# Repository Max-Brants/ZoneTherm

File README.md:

<picture>
  <source media="(prefers-color-scheme: dark)" srcset="brand/zonetherm-logo-dark.svg">
  
</picture>

# ZoneTherm

**A 7-zone OpenTherm heating/cooling controller.** ESP32-S3 firmware, KiCad
hardware, and a Svelte web UI for a house where every room has its own
OpenTherm room thermostat but the plant has a single manifold of zone valves.

Version 1.0.0.

---

## The idea

A normal OpenTherm setup is one thermostat talking to one boiler. ZoneTherm sits
in the middle of seven of those conversations at once:

```
 Room thermostat 1  ──OpenTherm──┐
 Room thermostat 2  ──OpenTherm──┤
        ...                      ├──►  ZoneTherm  ──I²C──►  MCP23017  ──►  7 zone valves
 Room thermostat 7  ──OpenTherm──┘        │
                                          ├──► Ethernet / WiFi ──► MQTT ──► Home Assistant
                                          └──► Web UI + REST API
```

To each thermostat, ZoneTherm **pretends to be a boiler**. It answers every
OpenTherm request the thermostat makes, so the thermostat behaves exactly as it
would on a real appliance — it shows a flame, it runs its own schedule, it lets
you turn the dial. While answering, ZoneTherm captures the two numbers that
matter: the room temperature the thermostat measured, and the setpoint it is
asking for.

It then makes the only decision that is actually its own: for each thermostat,
should heat be flowing? That is a bang-bang comparison with a symmetric
hysteresis band, and it lives in exactly one function
([`ClimateLogic::valveWanted`](Code/src/domain/ClimateLogic.h)).

Each thermostat drives a **valve set** — one valve, or several. A room with
three underfloor loops has three actuators and one thermostat, and they open
and close together in a single I²C write.
[`ValvePlan::solve`](Code/src/domain/ValvePlan.h) turns the seven per-room
answers into the one byte the expander wants. A valve belongs to at most one
thermostat, which the web UI enforces by greying out valves already taken and
the API enforces by rejecting the save.

One **season** — heating or cooling — applies to the whole plant, because
there is one set of pipes. Individual zones can be disabled, but they cannot
disagree about which direction the water is going.

Setpoints can also be pushed the other way. A setpoint sent from Home Assistant
or the web UI is written back to the room thermostat over OpenTherm's
`TrOverride` mechanism, so the wall unit shows the new target too.

### Things worth knowing before you build one

- ZoneTherm **is not a gateway.** There is no upstream boiler connection in the
  main firmware. It terminates all seven OpenTherm links itself and drives
  valves; your boiler is expected to be commanded by something else (a valve
  end-switch loop, or its own thermostat input).
- A zone whose thermostat has never reported a room temperature keeps its valves
  **closed**, as does a disabled zone. There is no fail-open.
- The same goes for the two ways a valve set can be misconfigured: a thermostat
  with **no valves** keeps tracking its band and reporting demand but opens
  nothing, and a valve **claimed by nobody** never opens. Both are flagged on
  the config page and logged at boot rather than silently guessed at.
- Upgrading from a pre-valve-set firmware leaves the wiring alone: every
  thermostat comes up owning the one valve on its own channel, exactly as
  before.
- `boilerTemp`, `flameOn`, `fault` and friends exist in the zone state and are
  parsed off the wire, but only `modulation` is currently exported as a Home
  Assistant sensor.

---

## Repository layout

| Path | What it is |
|---|---|
| [Code/](Code/) | ESP32-S3 firmware (ESP-IDF via PlatformIO). See [Code/README.md](Code/README.md) for the architecture write-up. |
| [Code/webui/](Code/webui/) | Svelte 5 + Vite + TypeScript single-page app, built into `Code/data/` and flashed as a LittleFS image. |
| [pcb/](pcb/) | KiCad 8 project `ZoneTherm.kicad_pro` — seven OpenTherm slave interfaces, W5500 Ethernet, MCP23017 valve bank. Fabrication outputs in `GERBER/`, `production/`, `jlcpcb/`. |
| [enclosure/](enclosure/) | Three-part printed case, generated from the KiCad board by a script rather than measured off it. See [enclosure/README.md](enclosure/README.md) — **read the mains section before printing one**. |
| [.github/workflows/](.github/workflows/) | Release workflow that builds and publishes the OTA assets. |

---

## Hardware

**Board:** ESP32-S3-DevKitC-1 (16 MB flash, no PSRAM required).

**Pinout** — from [`Code/src/app/Pins.h`](Code/src/app/Pins.h), matching the
`Thermos_In_X` / `Thermos_Out_X` nets on the schematic:

| Zone | In (GPIO) | Out (GPIO) |
|---|---|---|
| 1 | 2 | 1 |
| 2 | 42 | 41 |
| 3 | 40 | 39 |
| 4 | 48 | 47 |
| 5 | 20 | 19 |
| 6 | 18 | 17 |
| 7 | 16 | 15 |

I²C to the MCP23017 valve expander: `SDA = 4`, `SCL = 5`.
Ethernet is a W5500 on SPI — see U3 on `ZoneTherm.kicad_pcb`.

**Flash layout** ([`Code/partitions.csv`](Code/partitions.csv)) — dual OTA app
slots plus a large filesystem, which is what makes both firmware *and* web UI
updatable over the air:

| Partition | Offset | Size |
|---|---|---|
| `nvs` | 0x9000 | 16 KB |
| `otadata` | 0xd000 | 8 KB |
| `ota_0` | 0x10000 | 3 MB |
| `ota_1` | 0x310000 | 3 MB |
| `littlefs` | 0x610000 | ~10 MB |

---

## Getting started

### 1. Build and flash

PlatformIO is the primary path. On Windows, `pio` may not be on `PATH` —
`~/.platformio/penv/Scripts/platformio.exe` is the full path.

```bash
cd Code
pio run                 # build firmware
pio run -t upload       # flash over USB
pio run -t buildfs      # build the web UI into data/ and pack a LittleFS image
pio run -t uploadfs     # flash the filesystem
pio run -t monitor      # serial console @ 115200
```

`buildfs`/`uploadfs` run [`webui_build.py`](Code/webui_build.py) first, so the
image always contains the current `webui/src` rather than a stale `data/`.

Raw ESP-IDF (`idf.py build`) also works.

**Flash both** the firmware and the filesystem on a new board. Firmware alone
boots but serves no web UI.

### 2. First boot

Network bring-up is automatic and layered:

1. **Ethernet** (DHCP, zero configuration) is tried first and always wins — if
   the link comes up at any later point, WiFi is shut down and Ethernet takes
   over.
2. No Ethernet link → joins the configured **WiFi** as a station.
3. No WiFi configured, or it never gets an IP within 60 s → opens an open
   provisioning access point **`ZoneTherm-<ID>`** at <http://192.168.4.1/>.

`<ID>` is the last three bytes of the MAC in hex, so each controller is
distinct on a shared network.

The device also advertises itself over mDNS as `zonetherm-<ID>.local`.

### 3. Configure

Everything is runtime-configurable — **no credentials live in the source
tree**. Open `http://<device>/config` (or `POST /api/config`) and set:

- hostname
- WiFi SSID / password
- MQTT broker host, port, username, password, base topic, discovery prefix
- season (heating / cooling)
- valve hysteresis
- per-zone name, enabled flag, and valve set
- update repo, check interval, auto-install, include-filesystem

Settings persist in NVS namespace `otcfg`. `POST /api/factory-reset` erases it.

---

## Web UI and REST API

The SPA is served from LittleFS at `/` (zones), `/diagnostics` (thermostat
links and controller state; `/thermostats` is the old name and still works),
`/config` (settings) and `/update`. `/restart` and a 404 page are standalone
HTML so they still render while the device is rebooting or when assets are
missing. The visual identity is documented in [brand/](brand/).

| Endpoint | Method | Purpose |
|---|---|---|
| `/api/system` | GET | hostname, ip, mac, network, heap, uptime, cpuFreq, flashSize, sdkVersion, fwVersion, mode |
| `/api/thermostats` | GET | all seven zones (see below) |
| `/api/config` | GET / POST | full runtime config; secrets are masked on read |
| `/api/system/mode` | POST | set the plant season |
| `/api/thermostat/<1-7>/settemp` | POST | `temp=` — pushes a setpoint to the thermostat via TrOverride |
| `/api/thermostat/<1-7>/setname` | POST | `name=` — 1–32 characters |
| `/api/thermostat/<1-7>/enable` | POST | `enabled=true\|false` |
| `/api/factory-reset` | POST | wipe NVS |
| `/api/update` | GET | updater status |
| `/api/update/check` | POST | check GitHub for a newer release now |
| `/api/update/install` | POST | install the discovered release |
| `/ota/start`, `/update` | GET / POST | manual firmware/filesystem image upload |

Each zone in `/api/thermostats` carries: `id`, `name`, `enabled`, `status`
(`Active`/`Inactive`), `currentTemp`, `setpoint`, `modulation`,
`valves`, `valveOpen`, `action`, `errorCode`, `totalRequests`, `failedRequests`.

`valves` is the set this thermostat drives, as 1-based valve numbers —
`"valves": [1, 2, 3]` for a room with three loops. `valveOpen` means *at least
one of them is open*, so it is false for a thermostat that owns none. The same
array is read and written by `/api/config`; a `POST` that gives one valve to two
thermostats is rejected with `400` and changes nothing:

```bash
curl -X POST http://zonetherm.local/api/config -H 'Content-Type: application/json' \
  -d '{"zones":[{"id":1,"valves":[1,2,3]},{"id":2,"valves":[4,5]}]}'
```

---

## MQTT and Home Assistant

Set a broker on `/config` and ZoneTherm publishes **Home Assistant MQTT
auto-discovery** itself — no YAML. You get one `climate` entity plus a
modulation sensor per zone.

Base topic defaults to `zonetherm/<ID>` and is configurable. Per zone `N`
(1–7):

**Published state**

| Topic | Payload |
|---|---|
| `thermostat/N/temperature` | current room temperature |
| `thermostat/N/setpoint/state` | active setpoint |
| `thermostat/N/mode/state` | `off` \| `heat` \| `cool` |
| `thermostat/N/action` | `off` \| `idle` \| `heating` \| `cooling` |
| `thermostat/N/modulation` | % |
| `thermostat/N/state` | JSON attributes blob |

**Subscribed commands**

| Topic | Payload |
|---|---|
| `thermostat/N/setpoint/command` | target temperature |
| `thermostat/N/mode/command` | `off` disables the zone; `heat`/`cool` enables it |
| `system/mode/command` | `heating` \| `cooling` |

**Plant-wide:** `system/mode/state` and `status` are retained; `status` is also
the last-will topic, so an unplugged controller shows as unavailable in Home
Assistant rather than silently freezing at its last values.

Zone state is republished every 30 s, and immediately on a change.

A zone's HA climate mode maps onto the zone's enabled flag: `off` = disabled,
`heat`/`cool` = enabled under the current season. You cannot put one zone into
cooling while the rest heat — that is a plant-level setting.

---

## Over-the-air updates

ZoneTherm can pull its own releases from GitHub. Configure the repo
(`owner/name`) and interval on `/config`; the default is a 24 h check with
**notify-only** behaviour, so nothing installs without a click unless you
enable auto-install.

Version discovery deliberately **avoids the GitHub REST API**: this board has
no PSRAM, and a `/releases/latest` JSON body would have to be buffered and
parsed on a heap already shared with the HTTP server, MQTT and the OpenTherm
engine. Instead the updater requests `https://github.com/<repo>/releases/latest`
with redirects disabled and reads the tag out of the 302 `Location` header —
one request, zero body bytes, no rate limit, and it works for hand-made
releases. Assets then live at predictable
`.../releases/download/<tag>/{firmware.bin,littlefs.bin}` URLs.

Pushing a `v*` tag runs [`release.yml`](.github/workflows/release.yml), which
stamps the tag into `Version.h`, builds both images, trims the ~10 MB of erased
padding off `littlefs.bin`, and publishes them with a `SHA256SUMS.txt`.

Two constraints worth knowing:

- **The device only installs a strictly newer semver.** With 1.0.0 flashed, tag
  `v1.0.1` to actually exercise the updater.
- **Rollback needs one serial flash to arm.** `CONFIG_BOOTLOADER_APP_ROLLBACK_ENABLE`
  is set, and an OTA image boots on probation — `UpdateService` only confirms it
  once the network is up, so a release that cannot get online reverts instead of
  stranding the controller. But the revert logic lives in the *bootloader*, which
  cannot be delivered over the air. Devices flashed before this option was added
  keep the old bootloader until reflashed over USB.
- Asset filenames are hard-coded device-side. Renaming one silently breaks every
  deployed controller.

---

## Architecture at a glance

Full write-up in [Code/README.md](Code/README.md). The short version:

- `Main.cpp` is the composition root — every object is built there and wired by
  reference. No singletons.
- `domain/` is pure logic with no ESP-IDF includes — the frame codec, the request
  responder, the zone registry, the per-room valve decision and the valve-set
  aggregation — so it can be compiled off-device.
- A dedicated `ot_task` (core 1, priority 15) owns all OpenTherm I/O. Responses
  are transmitted 40 ms after the request **by deadline** rather than by
  sleeping, so one channel cannot stall the other six.
- The main task ticks network, valves, MQTT and the updater at 1 Hz.
- All shared zone state lives in `ZoneRegistry` behind a single mutex; callers
  only ever receive value snapshots, never references into locked state.

---

## Credits and licensing

ZoneTherm is released under the MIT License — see [LICENSE](LICENSE).

Third-party code lives in `Code/src/vendor/`. Both libraries keep their upstream
register maps, frame logic and public APIs; only the hardware touchpoints were
rewritten for native ESP-IDF:

- **OpenTherm library** — [ihormelnyk/OpenTherm](https://github.com/ihormelnyk/OpenTherm),
  MIT, © 2023 Ihor Melnyk. Ported from Arduino to native ESP-IDF GPIO/timer APIs.
- **MCP23017 driver** — [blemasle/arduino-mcp23017](https://github.com/blemasle/arduino-mcp23017),
  MIT, © 2017 Bertrand Lemasle. Ported from Arduino `Wire` to `driver/i2c_master.h`.

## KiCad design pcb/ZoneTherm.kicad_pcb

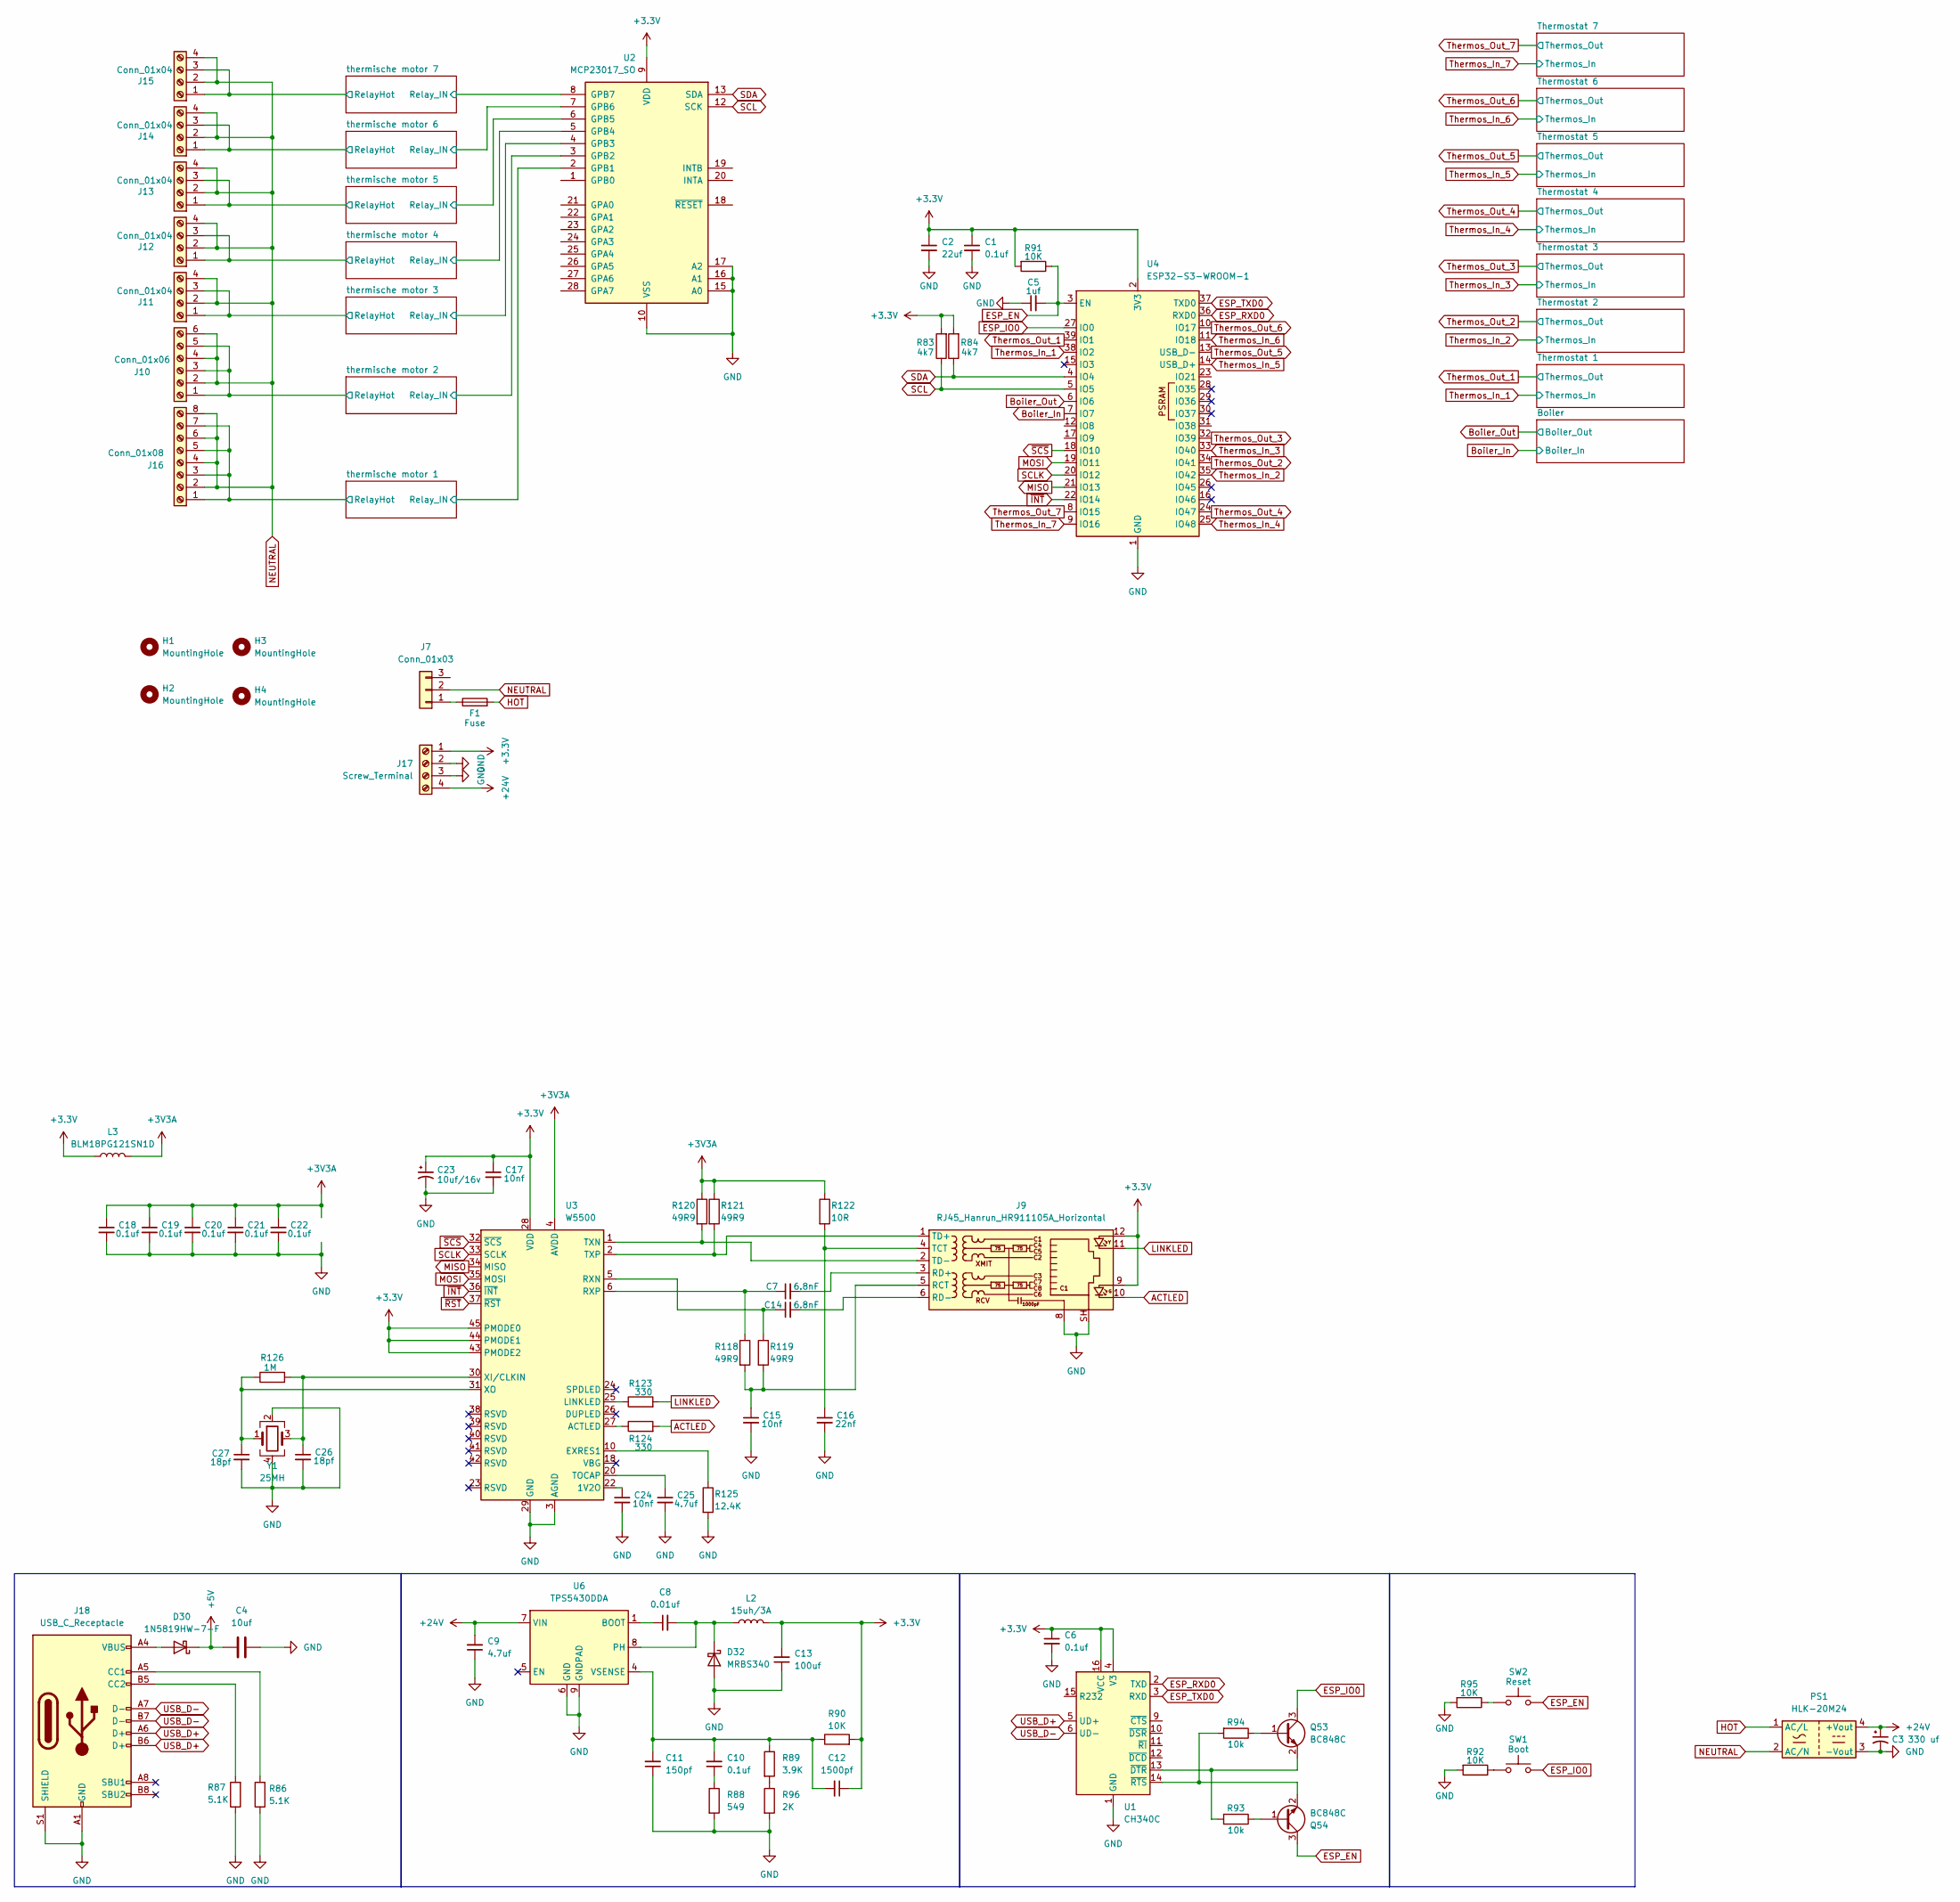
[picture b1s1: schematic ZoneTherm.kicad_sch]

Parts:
C1, C10, C18, C19, C20, C21, C22: 0.1uf; C_0402_1005Metric
C2: 22uf; C_0603_1608Metric
C3: 330 uf; CP_Elec_8x10.5
C4: 10uf
C5: 1uf; C_0603_1608Metric
C6: 0.1uf; C_0603_1608Metric
C7, C14: 6.8nF; C_0402_1005Metric
C8: 0.01uf; C_0402_1005Metric
C9: 4.7uf; C_1206_3216Metric
C11: 150pf; C_0603_1608Metric
C12: 1500pf; C_0603_1608Metric
C13: 100uf; C_1206_3216Metric
C15, C17, C24: 10nf; C_0402_1005Metric
C16: 22nf; C_0402_1005Metric
C23: 10uf/16v; CP_EIA-3216-18_Kemet-A
C25: 4.7uf; C_0402_1005Metric
C26, C27: 18pf; C_0402_1005Metric
D30: 1N5819HW-7-F
D32: MRBS340; D_SMC
F1: Fuse; Fuseholder_Cylinder-5x20mm_Schurter_0031_8201_Horizontal_Op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
H1, H2, H3, H4: MountingHole; MountingHole_3.2mm_M3
J7: Conn_01x03; PhoenixContact_MSTBA_2,5_3-G-5,08_1x03_P5.08mm_Horizontal
J9: RJ45_Hanrun_HR911105A_Horizontal
J10: Conn_01x06; PhoenixContact_MSTBA_2,5_6-G-5,08_1x06_P5.08mm_Horizontal
J11, J12, J13, J14, J15: Conn_01x04; PhoenixContact_MSTBA_2,5_4-G-5,08_1x04_P5.08mm_Horizontal
J16: Conn_01x08; PhoenixContact_MSTBA_2,5_8-G-5,08_1x08_P5.08mm_Horizontal
J17: Screw_Terminal; Altech_AK100_1x04_P5.00mm
J18: USB_C_Receptacle; USB_C_Receptacle_Palconn_UTC16-G
L2: 15uh/3A; L_Changjiang_FXL0630
L3: BLM18PG121SN1D; L_0603_1608Metric
PS1: HLK-20M24; Converter_ACDC_Hi-Link_HLK-20Mxx
Q53, Q54: BC848C; SOT-23
R83, R84: 4k7; R_0603_1608Metric
R86, R87: 5.1K; R_0402_1005Metric
R88: 549; R_0603_1608Metric
R89: 3.9K; R_0603_1608Metric
R90, R91, R92, R95: 10K; R_0603_1608Metric
R93, R94: 10k; R_0603_1608Metric
R96: 2K; R_0603_1608Metric
R118, R119, R120, R121: 49R9; R_0402_1005Metric
R122: 10R; R_0402_1005Metric
R123, R124: 330; R_0402_1005Metric
R125: 12.4K; R_0402_1005Metric
R126: 1M; R_0402_1005Metric
SW1: Boot; SW-SMD_L3.9-W3.0-P4.45
SW2: Reset; SW-SMD_L3.9-W3.0-P4.45
U1: CH340C; SOIC-16_3.9x9.9mm_P1.27mm
U2: MCP23017_SO; SOIC-28W_7.5x17.9mm_P1.27mm
U3: W5500; LQFP-48_7x7mm_P0.5mm
U4: ESP32-S3-WROOM-1
U6: TPS5430DDA; TI_SO-PowerPAD-8
Y1: 25MH; Crystal_SMD_TXC_7M-4Pin_3.2x2.5mm

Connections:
+3.3V: C1.1, C2.1, C6.1, C12.1, C13.2, C17.1, C23.1, J9.9, J9.12, J17.1, L2.2, L3.1, R83.2, R84.2, R90.2, R91.2, U1.4 (V3), U1.16 (VCC), U2.9 (VDD), U3.28 (VDD), U3.43 (PMODE2), U3.44 (PMODE1), U3.45 (PMODE0), U4.2 (3V3); also elsewhere on the board
+3V3A: C18.1, C19.1, C20.1, C21.1, C22.1, L3.2, R120.1, R121.1, R122.1, U3.4 (AVDD), U3.8 (AVDD), U3.11 (AVDD), U3.15 (AVDD), U3.17 (AVDD), U3.21 (AVDD)
+24V: C3.1, C9.2, J17.4, PS1.4 (+Vout), U6.7 (VIN); also elsewhere on the board
/thermische motor 1/RelayHot: J16.1, J16.3, J16.5, J16.7; also elsewhere on the board
/thermische motor 1/Relay_IN: U2.2 (GPB1); also elsewhere on the board
/thermische motor 2/RelayHot: J10.1, J10.3, J10.5; also elsewhere on the board
/thermische motor 2/Relay_IN: U2.3 (GPB2); also elsewhere on the board
/thermische motor 3/RelayHot: J11.1, J11.3; also elsewhere on the board
/thermische motor 3/Relay_IN: U2.4 (GPB3); also elsewhere on the board
/thermische motor 4/RelayHot: J12.1, J12.3; also elsewhere on the board
/thermische motor 4/Relay_IN: U2.5 (GPB4); also elsewhere on the board
/thermische motor 5/RelayHot: J13.1, J13.3; also elsewhere on the board
/thermische motor 5/Relay_IN: U2.6 (GPB5); also elsewhere on the board
/thermische motor 6/RelayHot: J14.1, J14.3; also elsewhere on the board
/thermische motor 6/Relay_IN: U2.7 (GPB6); also elsewhere on the board
/thermische motor 7/RelayHot: J15.1, J15.3; also elsewhere on the board
/thermische motor 7/Relay_IN: U2.8 (GPB7); also elsewhere on the board
ACTLED: J9.10, R124.2
Boiler_In: U4.7 (IO7); also elsewhere on the board
Boiler_Out: U4.6 (IO6); also elsewhere on the board
ESP_EN: C5.2, Q54.3 (C), R91.1, SW2.2, U4.3 (EN)
ESP_IO0: Q53.3 (C), SW1.2, U4.27 (IO0)
ESP_RXD0: U1.2 (TXD), U4.36 (RXD0)
ESP_TXD0: U1.3 (RXD), U4.37 (TXD0)
GND: C1.2, C2.2, C3.2, C4.1, C5.1, C6.2, C9.1, C11.1, C13.1, C15.2, C16.2, C17.2, C18.2, C19.2, C20.2, C21.2, C22.2, C23.2, C24.2, C25.2, C26.2, C27.2, D32.2 (A), J9.8, J9.SH, J17.2, J17.3, J18.A1 (GND), J18.A12 (GND), J18.B1 (GND), J18.B12 (GND), J18.S1 (SHIELD), PS1.3 (-Vout), R86.1, R87.1, R88.2, R92.2, R95.2, R96.2, R125.2, U1.1 (GND), U2.10 (VSS), U2.15 (A0), U2.16 (A1), U2.17 (A2), U3.3 (AGND), U3.9 (AGND), U3.14 (AGND), U3.16 (AGND), U3.19 (AGND), U3.29 (GND), U3.48 (AGND), U4.1 (GND), U4.40 (GND), U4.41 (GND), U6.6 (GND), U6.9 (GNDPAD), Y1.2, Y1.4; also elsewhere on the board
HOT: F1.2, PS1.1 (AC/L); also elsewhere on the board
LINKLED: J9.11, R123.2
MISO: U3.34 (MISO), U4.21 (IO13)
MOSI: U3.35 (MOSI), U4.19 (IO11)
NEUTRAL: J7.2, J10.2, J10.4, J10.6, J11.2, J11.4, J12.2, J12.4, J13.2, J13.4, J14.2, J14.4, J15.2, J15.4, J16.2, J16.4, J16.6, J16.8, PS1.2 (AC/N)
unnamed: C4.2, D30.1 (K)
unnamed: C10.1, R88.1
unnamed: C8.2, D32.1 (K), L2.1, U6.8 (PH)
unnamed: F1.1, J7.1
unnamed: C15.1, J9.5 (RCT), R118.2, R119.2
unnamed: C7.2, J9.3 (RD+)
unnamed: C14.2, J9.6 (RD-)
unnamed: C16.1, J9.4 (TCT), R122.2
unnamed: J9.1 (TD+), R121.2, U3.2 (TXP)
unnamed: J9.2 (TD-), R120.2, U3.1 (TXN)
unnamed: J18.A5 (CC1), R86.2
unnamed: J18.B5 (CC2), R87.2
unnamed: D30.2 (A), J18.A4 (VBUS), J18.A9 (VBUS), J18.B4 (VBUS), J18.B9 (VBUS)
unnamed: Q53.1 (B), R94.1
unnamed: Q53.2 (E), R93.2, U1.13 (~DTR)
unnamed: Q54.1 (B), R93.1
unnamed: Q54.2 (E), R94.2, U1.14 (~RTS)
unnamed: R89.2, R96.1
unnamed: R92.1, SW1.1
unnamed: R95.1, SW2.1
unnamed: C24.1, U3.22 (1V2O)
unnamed: R124.1, U3.27 (ACTLED)
unnamed: R125.1, U3.10 (EXRES1)
unnamed: R123.1, U3.25 (LINKLED)
unnamed: C14.1, R119.1, U3.5 (RXN)
unnamed: C7.1, R118.1, U3.6 (RXP)
unnamed: C25.1, U3.20 (TOCAP)
unnamed: C26.1, R126.2, U3.30 (XI/CLKIN), Y1.3
unnamed: C27.1, R126.1, U3.31 (XO), Y1.1
unnamed: C8.1, U6.1 (BOOT)
unnamed: C10.2, C11.2, C12.2, R89.1, R90.1, U6.4 (VSENSE)
SCL: R83.1, U2.12 (SCK), U4.5 (IO5)
SCLK: U3.33 (SCLK), U4.20 (IO12)
SDA: R84.1, U2.13 (SDA), U4.4 (IO4)
Thermos_In_1: U4.38 (IO2); also elsewhere on the board
Thermos_In_2: U4.35 (IO42); also elsewhere on the board
Thermos_In_3: U4.33 (IO40); also elsewhere on the board
Thermos_In_4: U4.25 (IO48); also elsewhere on the board
Thermos_In_5: U4.14 (USB_D+); also elsewhere on the board
Thermos_In_6: U4.11 (IO18); also elsewhere on the board
Thermos_In_7: U4.9 (IO16); also elsewhere on the board
Thermos_Out_1: U4.39 (IO1); also elsewhere on the board
Thermos_Out_2: U4.34 (IO41); also elsewhere on the board
Thermos_Out_3: U4.32 (IO39); also elsewhere on the board
Thermos_Out_4: U4.24 (IO47); also elsewhere on the board
Thermos_Out_5: U4.13 (USB_D-); also elsewhere on the board
Thermos_Out_6: U4.10 (IO17); also elsewhere on the board
Thermos_Out_7: U4.8 (IO15); also elsewhere on the board
USB_D+: J18.A6 (D+), J18.B6 (D+), U1.5 (UD+)
USB_D-: J18.A7 (D-), J18.B7 (D-), U1.6 (UD-)
~INT: U3.36 (~INT), U4.22 (IO14)
~RST: U3.37 (~RST)
~SCS: U3.32 (~SCS), U4.18 (IO10)

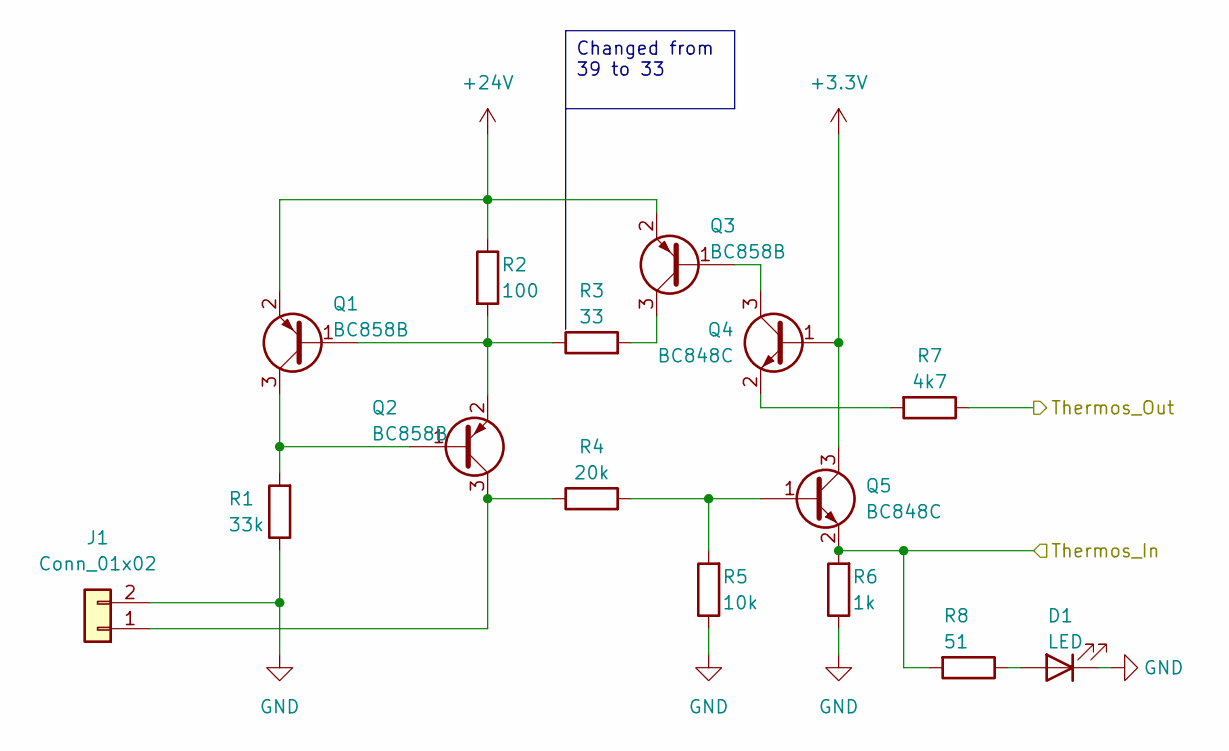
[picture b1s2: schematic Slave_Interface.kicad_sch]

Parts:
D1: LED; LED_0805_2012Metric
J1: Conn_01x02; PhoenixContact_MSTBA_2,5_2-G-5,08_1x02_P5.08mm_Horizontal
Q1, Q2, Q3: BC858B; SOT-23
Q4, Q5: BC848C; SOT-23
R1: 33k; R_0603_1608Metric
R2: 100; R_0603_1608Metric
R3: 33; R_0603_1608Metric
R4: 20k; R_0603_1608Metric
R5: 10k; R_0603_1608Metric
R6: 1k; R_0603_1608Metric
R7: 4k7; R_0603_1608Metric
R8: 51; R_0603_1608Metric

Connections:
+3.3V: Q4.1 (B), Q5.3 (C); also elsewhere on the board
+24V: Q1.2 (E), Q3.2 (E), R2.1; also elsewhere on the board
GND: D1.1 (K), J1.2, R1.1, R5.1, R6.1; also elsewhere on the board
unnamed: D1.2 (A), R8.1
unnamed: J1.1, Q2.3 (C), R4.1
unnamed: Q1.1 (B), Q2.2 (E), R2.2, R3.1
unnamed: Q1.3 (C), Q2.1 (B), R1.2
unnamed: Q3.1 (B), Q4.3 (C)
unnamed: Q3.3 (C), R3.2
unnamed: Q4.2 (E), R7.2
unnamed: Q5.1 (B), R4.2, R5.2
Thermos_In_1: Q5.2 (E), R6.2, R8.2; also elsewhere on the board
Thermos_Out_1: R7.1; also elsewhere on the board

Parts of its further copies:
D2, D3, D4, D5, D6, D7: LED; LED_0805_2012Metric
J2, J3, J4, J5, J6, J8: Conn_01x02; PhoenixContact_MSTBA_2,5_2-G-5,08_1x02_P5.08mm_Horizontal
Q6, Q7, Q8, Q11, Q12, Q13, Q16, Q17, Q18, Q21, Q22, Q23, Q26, Q27, Q28, Q39, Q40, Q41: BC858B; SOT-23
Q9, Q10, Q14, Q15, Q19, Q20, Q24, Q25, Q29, Q30, Q42, Q43: BC848C; SOT-23
R9, R16, R25, R33, R41, R68: 33k; R_0603_1608Metric
R10, R17, R26, R34, R42, R69: 100; R_0603_1608Metric
R11, R18, R27, R35, R43, R70: 33; R_0603_1608Metric
R12, R19, R28, R36, R44, R71: 20k; R_0603_1608Metric
R13, R20, R29, R37, R45, R72: 10k; R_0603_1608Metric
R14, R21, R30, R38, R46, R73: 1k; R_0603_1608Metric
R15, R22, R31, R39, R47, R74: 4k7; R_0603_1608Metric
R23, R24, R32, R40, R48, R75: 51; R_0603_1608Metric

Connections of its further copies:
+3.3V: Q9.1 (B), Q10.3 (C), Q14.1 (B), Q15.3 (C), Q19.1 (B), Q20.3 (C), Q24.1 (B), Q25.3 (C), Q29.1 (B), Q30.3 (C), Q42.1 (B), Q43.3 (C); also elsewhere on the board
+24V: Q6.2 (E), Q8.2 (E), Q11.2 (E), Q13.2 (E), Q16.2 (E), Q18.2 (E), Q21.2 (E), Q23.2 (E), Q26.2 (E), Q28.2 (E), Q39.2 (E), Q41.2 (E), R10.1, R17.1, R26.1, R34.1, R42.1, R69.1; also elsewhere on the board
GND: D2.1 (K), D3.1 (K), D4.1 (K), D5.1 (K), D6.1 (K), D7.1 (K), J2.2, J3.2, J4.2, J5.2, J6.2, J8.2, R9.1, R13.1, R14.1, R16.1, R20.1, R21.1, R25.1, R29.1, R30.1, R33.1, R37.1, R38.1, R41.1, R45.1, R46.1, R68.1, R72.1, R73.1; also elsewhere on the board
unnamed: D2.2 (A), R23.1
unnamed: D3.2 (A), R24.1
unnamed: D4.2 (A), R32.1
unnamed: D5.2 (A), R40.1
unnamed: D6.2 (A), R48.1
unnamed: D7.2 (A), R75.1
unnamed: J2.1, Q12.3 (C), R19.1
unnamed: J3.1, Q7.3 (C), R12.1
unnamed: J4.1, Q17.3 (C), R28.1
unnamed: J5.1, Q22.3 (C), R36.1
unnamed: J6.1, Q27.3 (C), R44.1
unnamed: J8.1, Q40.3 (C), R71.1
unnamed: Q6.1 (B), Q7.2 (E), R10.2, R11.1
unnamed: Q6.3 (C), Q7.1 (B), R9.2
unnamed: Q8.1 (B), Q9.3 (C)
unnamed: Q8.3 (C), R11.2
unnamed: Q9.2 (E), R15.2
unnamed: Q10.1 (B), R12.2, R13.2
unnamed: Q11.1 (B), Q12.2 (E), R17.2, R18.1
unnamed: Q11.3 (C), Q12.1 (B), R16.2
unnamed: Q13.1 (B), Q14.3 (C)
unnamed: Q13.3 (C), R18.2
unnamed: Q14.2 (E), R22.2
unnamed: Q15.1 (B), R19.2, R20.2
unnamed: Q16.1 (B), Q17.2 (E), R26.2, R27.1
unnamed: Q16.3 (C), Q17.1 (B), R25.2
unnamed: Q18.1 (B), Q19.3 (C)
unnamed: Q18.3 (C), R27.2
unnamed: Q19.2 (E), R31.2
unnamed: Q20.1 (B), R28.2, R29.2
unnamed: Q21.1 (B), Q22.2 (E), R34.2, R35.1
unnamed: Q21.3 (C), Q22.1 (B), R33.2
unnamed: Q23.1 (B), Q24.3 (C)
unnamed: Q23.3 (C), R35.2
unnamed: Q24.2 (E), R39.2
unnamed: Q25.1 (B), R36.2, R37.2
unnamed: Q26.1 (B), Q27.2 (E), R42.2, R43.1
unnamed: Q26.3 (C), Q27.1 (B), R41.2
unnamed: Q28.1 (B), Q29.3 (C)
unnamed: Q28.3 (C), R43.2
unnamed: Q29.2 (E), R47.2
unnamed: Q30.1 (B), R44.2, R45.2
unnamed: Q39.1 (B), Q40.2 (E), R69.2, R70.1
unnamed: Q39.3 (C), Q40.1 (B), R68.2
unnamed: Q41.1 (B), Q42.3 (C)
unnamed: Q41.3 (C), R70.2
unnamed: Q42.2 (E), R74.2
unnamed: Q43.1 (B), R71.2, R72.2
Thermos_In_2: Q15.2 (E), R21.2, R23.2; also elsewhere on the board
Thermos_In_3: Q10.2 (E), R14.2, R24.2; also elsewhere on the board
Thermos_In_4: Q20.2 (E), R30.2, R32.2; also elsewhere on the board
Thermos_In_5: Q25.2 (E), R38.2, R40.2; also elsewhere on the board
Thermos_In_6: Q30.2 (E), R46.2, R48.2; also elsewhere on the board
Thermos_In_7: Q43.2 (E), R73.2, R75.2; also elsewhere on the board
Thermos_Out_2: R22.1; also elsewhere on the board
Thermos_Out_3: R15.1; also elsewhere on the board
Thermos_Out_4: R31.1; also elsewhere on the board
Thermos_Out_5: R39.1; also elsewhere on the board
Thermos_Out_6: R47.1; also elsewhere on the board
Thermos_Out_7: R74.1; also elsewhere on the board

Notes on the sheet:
Changed from 39 to 33

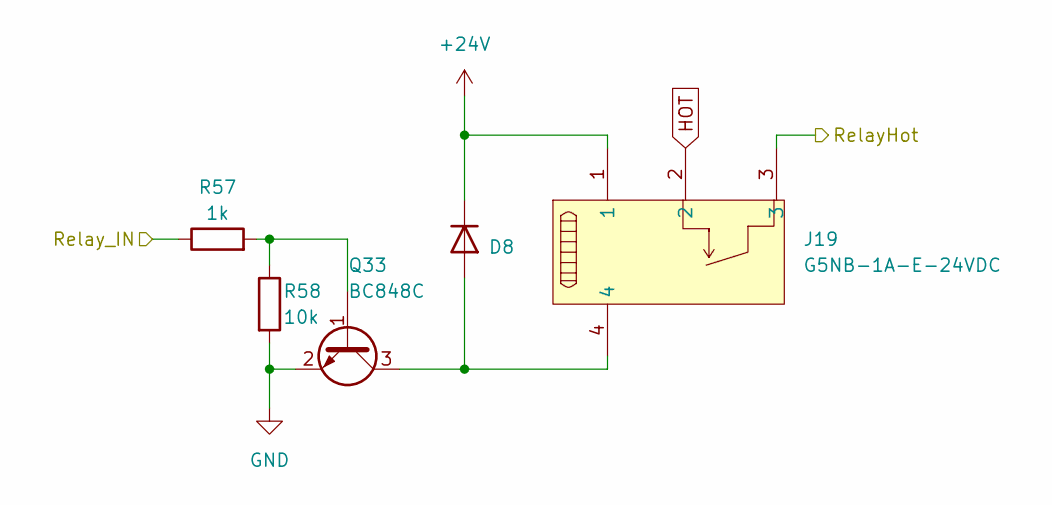
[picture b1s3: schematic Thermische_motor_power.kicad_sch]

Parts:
D8: 1N4148WS; D_SOD-323
J19: G5NB-1A-E-24VDC; RELAY-TH_G5NB-1A-E-24VDC; MPN G5NB-1A-E-24VDC; LCSC Part C34758
Q33: BC848C; SOT-23
R57: 1k; R_0603_1608Metric
R58: 10k; R_0603_1608Metric

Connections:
+24V: D8.1 (K), J19.1; also elsewhere on the board
/thermische motor 1/RelayHot: J19.3; also elsewhere on the board
/thermische motor 1/Relay_IN: R57.1; also elsewhere on the board
GND: Q33.2 (E), R58.2; also elsewhere on the board
HOT: J19.2; also elsewhere on the board
unnamed: D8.2 (A), J19.4, Q33.3 (C)
unnamed: Q33.1 (B), R57.2, R58.1

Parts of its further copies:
D9, D18, D19, D20, D21, D22: 1N4148WS; D_SOD-323
J20, J21, J22, J23, J25, J26: G5NB-1A-E-24VDC; RELAY-TH_G5NB-1A-E-24VDC; MPN G5NB-1A-E-24VDC; LCSC Part C34758
Q31, Q34, Q35, Q36, Q37, Q38: BC848C; SOT-23
R49, R51, R60, R62, R64, R66: 1k; R_0603_1608Metric
R50, R59, R61, R63, R65, R67: 10k; R_0603_1608Metric

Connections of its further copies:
+24V: D9.1 (K), D18.1 (K), D19.1 (K), D20.1 (K), D21.1 (K), D22.1 (K), J20.1, J21.1, J22.1, J23.1, J25.1, J26.1; also elsewhere on the board
/thermische motor 2/RelayHot: J20.3; also elsewhere on the board
/thermische motor 2/Relay_IN: R49.1; also elsewhere on the board
/thermische motor 3/RelayHot: J21.3; also elsewhere on the board
/thermische motor 3/Relay_IN: R51.1; also elsewhere on the board
/thermische motor 4/RelayHot: J22.3; also elsewhere on the board
/thermische motor 4/Relay_IN: R60.1; also elsewhere on the board
/thermische motor 5/RelayHot: J23.3; also elsewhere on the board
/thermische motor 5/Relay_IN: R62.1; also elsewhere on the board
/thermische motor 6/RelayHot: J25.3; also elsewhere on the board
/thermische motor 6/Relay_IN: R64.1; also elsewhere on the board
/thermische motor 7/RelayHot: J26.3; also elsewhere on the board
/thermische motor 7/Relay_IN: R66.1; also elsewhere on the board
GND: Q31.2 (E), Q34.2 (E), Q35.2 (E), Q36.2 (E), Q37.2 (E), Q38.2 (E), R50.2, R59.2, R61.2, R63.2, R65.2, R67.2; also elsewhere on the board
HOT: J20.2, J21.2, J22.2, J23.2, J25.2, J26.2; also elsewhere on the board
unnamed: D9.2 (A), J20.4, Q31.3 (C)
unnamed: D18.2 (A), J21.4, Q34.3 (C)
unnamed: D19.2 (A), J22.4, Q35.3 (C)
unnamed: D20.2 (A), J23.4, Q36.3 (C)
unnamed: D21.2 (A), J25.4, Q37.3 (C)
unnamed: D22.2 (A), J26.4, Q38.3 (C)
unnamed: Q31.1 (B), R49.2, R50.1
unnamed: Q34.1 (B), R51.2, R59.1
unnamed: Q35.1 (B), R60.2, R61.1
unnamed: Q36.1 (B), R62.2, R63.1
unnamed: Q37.1 (B), R64.2, R65.1
unnamed: Q38.1 (B), R66.2, R67.1

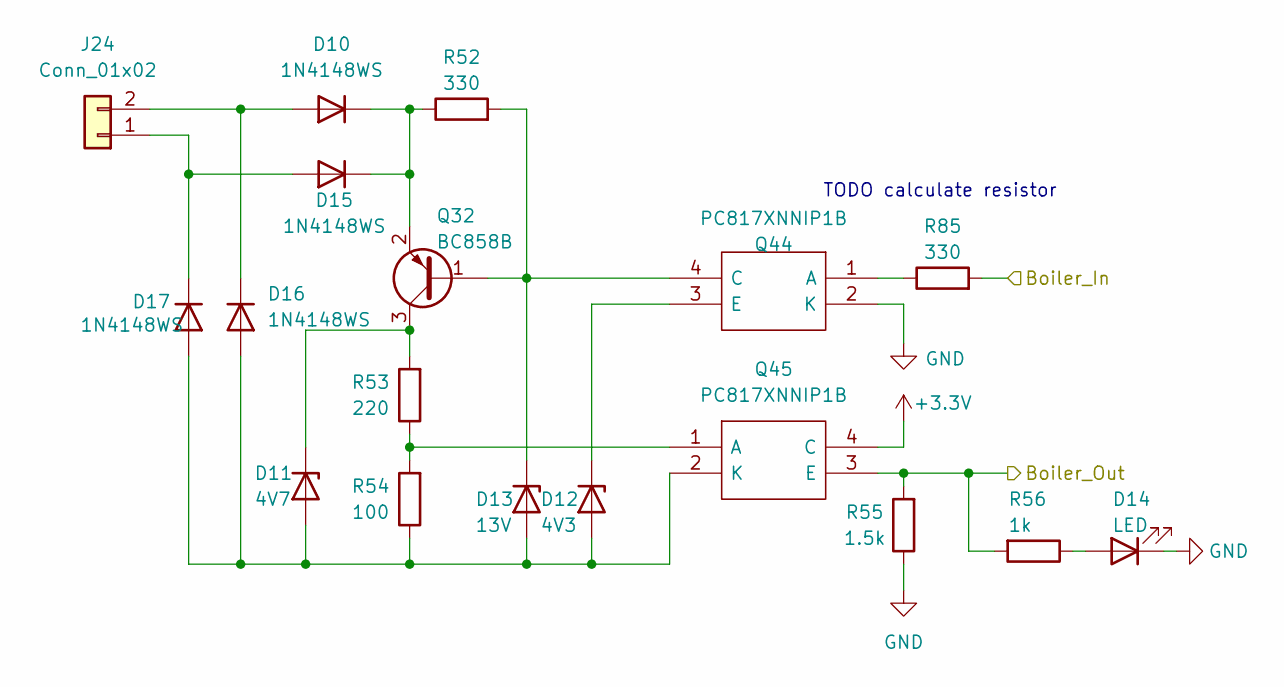
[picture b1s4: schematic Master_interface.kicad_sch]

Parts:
D10, D15, D16, D17: 1N4148WS; D_SOD-323
D11: 4V7; D_SOD-323_HandSoldering
D12: 4V3; D_SOD-323_HandSoldering
D13: 13V; D_SOD-323_HandSoldering
D14: LED; LED_0805_2012Metric
J24: Conn_01x02; PhoenixContact_MSTBA_2,5_2-G-5,08_1x02_P5.08mm_Horizontal
Q32: BC858B; SOT-23
Q44, Q45: PC817XNNIP1B; SOP254P960X420-4N; Manufacturer_Part_Number PC817XNNIP1B; Mouser Part Number 852-PC817XNNIP1B
R52, R85: 330; R_0603_1608Metric
R53: 220; R_0603_1608Metric
R54: 100; R_0603_1608Metric
R55: 1.5k; R_0603_1608Metric
R56: 1k; R_0603_1608Metric

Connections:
+3.3V: Q45.4 (C); also elsewhere on the board
Boiler_In: R85.2; also elsewhere on the board
Boiler_Out: Q45.3 (E), R55.2, R56.2; also elsewhere on the board
GND: D14.1 (K), Q44.2 (K), R55.1; also elsewhere on the board
unnamed: D10.2 (A), D16.1 (K), J24.2
unnamed: D10.1 (K), D15.1 (K), Q32.2 (E), R52.1
unnamed: D11.2 (A), D12.2 (A), D13.2 (A), D16.2 (A), D17.2 (A), Q45.2 (K), R54.1
unnamed: D11.1 (K), Q32.3 (C), R53.2
unnamed: D12.1 (K), Q44.3 (E)
unnamed: D13.1 (K), Q32.1 (B), Q44.4 (C), R52.2
unnamed: D14.2 (A), R56.1
unnamed: D15.2 (A), D17.1 (K), J24.1
unnamed: Q44.1 (A), R85.1
unnamed: Q45.1 (A), R53.1, R54.2

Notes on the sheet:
TODO calculate resistor
